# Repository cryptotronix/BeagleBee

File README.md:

BeagleBee
=========

Design files for the Cryptotronix BeagleBee Adapter available on [Tindie](https://www.tindie.com/products/cryptotronix/beaglebee/).

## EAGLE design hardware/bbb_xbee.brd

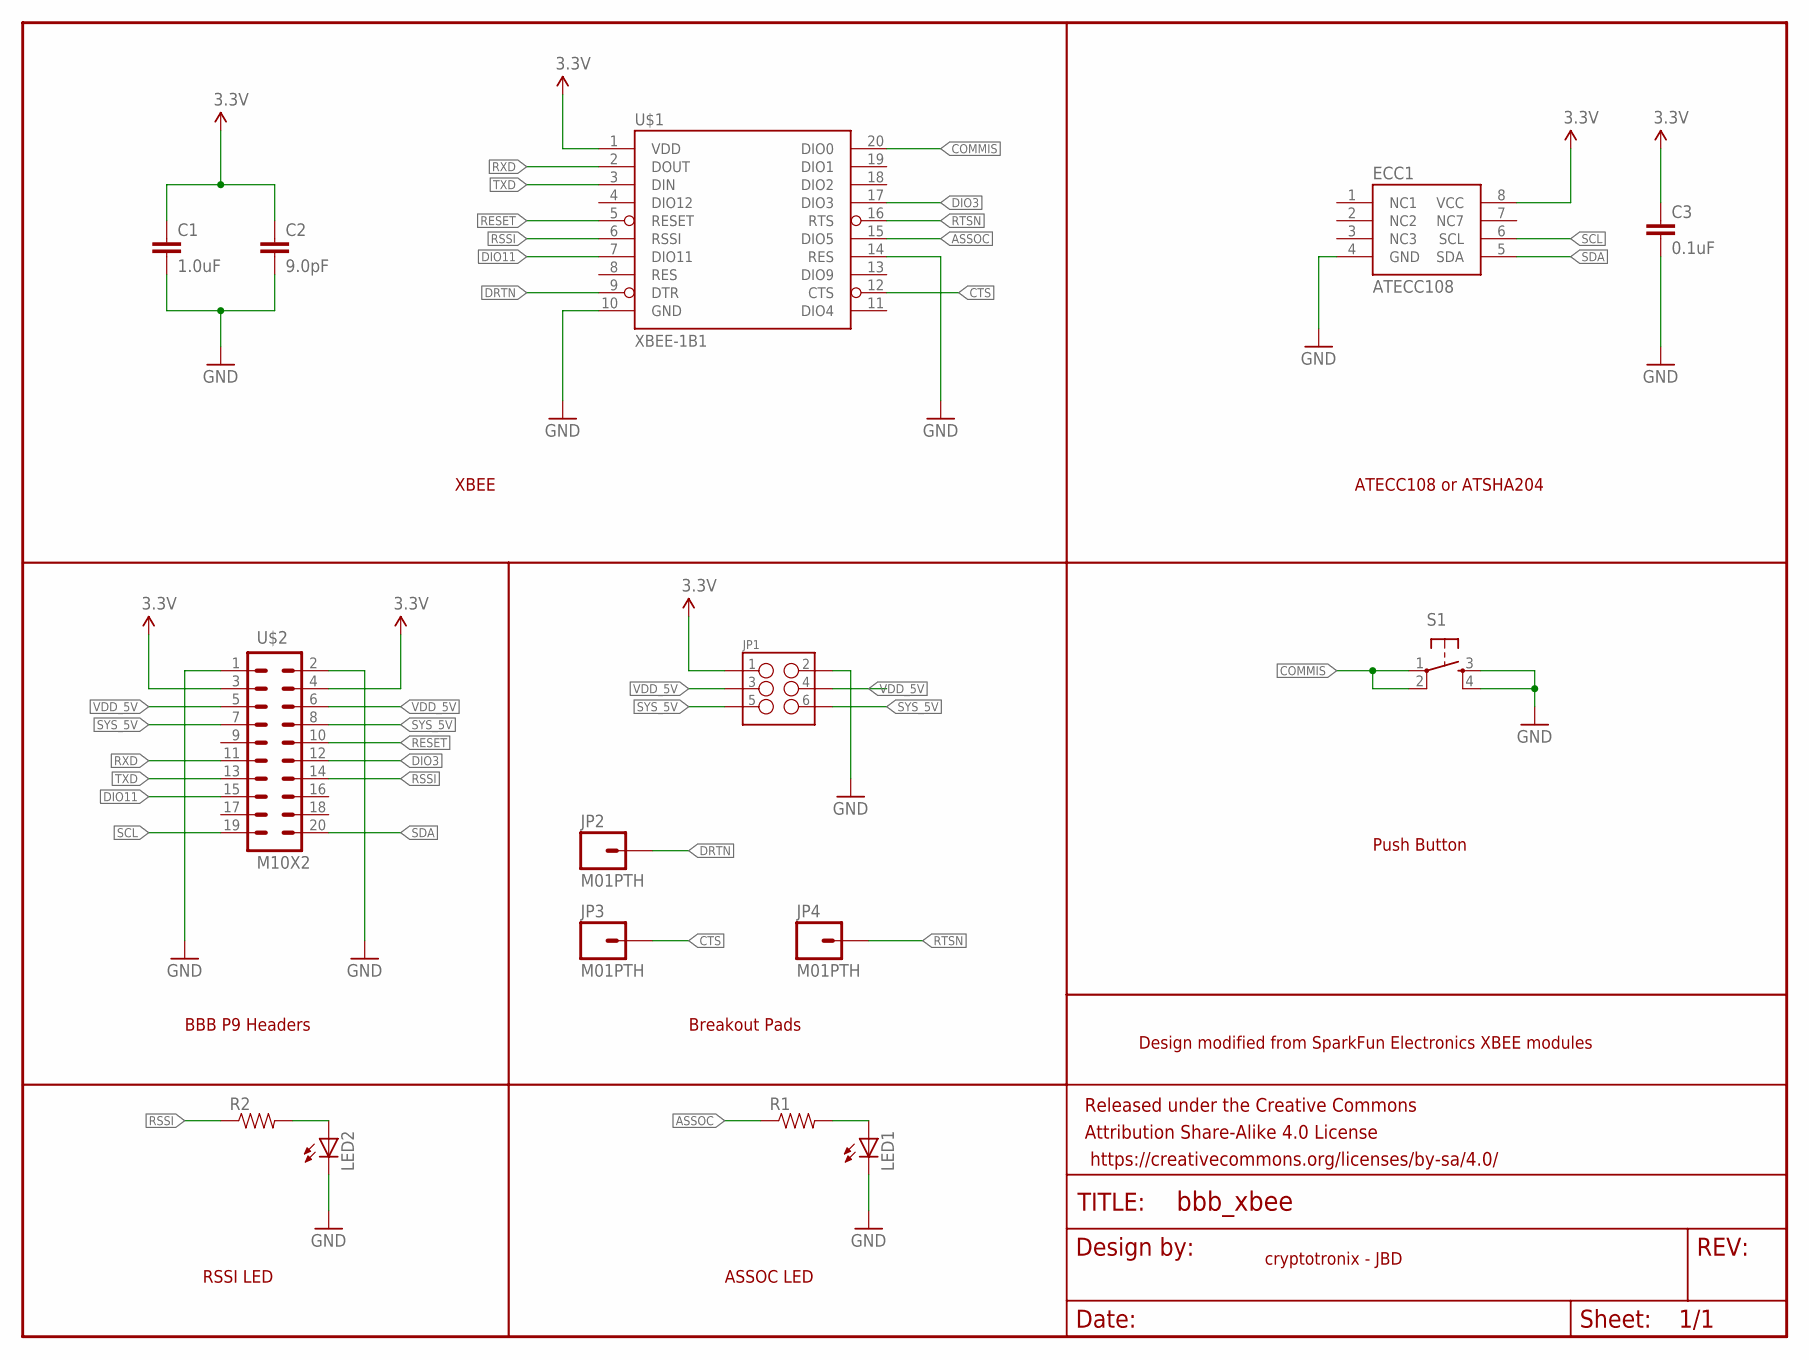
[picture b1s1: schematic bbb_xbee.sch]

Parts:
C1: 1.0uF; 0603-CAP
C2: 9.0pF; 0603-CAP
C3: 0.1uF; 0603-CAP
ECC1: ATECC108; SOIC8
FRAME1: FRAME-LETTER; CREATIVE_COMMONS
JP1: M03X22X3_SILK_SM; 2X3
JP2, JP3, JP4: M01PTH; 1X01
LED1: LED-RED0603; LED-0603
LED2: LED-BLUE0603; LED-0603
R1, R2: RESISTOR0603; 0603-RES
S1: TAC_SWITCHPTH; TACTILE-PTH
U$1: XBEE-1B1; XBEE-1
U$2: M10X2; 2X10

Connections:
3.3V: C1.1, C2.1, C3.1, ECC1.8 (VCC), JP1.1, U$1.1 (VDD), U$2.3, U$2.4
ASSOC: R1.1, U$1.15 (DIO5)
COMMIS: S1.1, S1.2, U$1.20 (DIO0)
CTS: JP3.1, U$1.12 (CTS)
DIO3: U$1.17 (DIO3), U$2.12
DIO11: U$1.7 (DIO11), U$2.15
DRTN: JP2.1, U$1.9 (DTR)
GND: C1.2, C2.2, C3.2, ECC1.4 (GND), JP1.2, LED1.C, LED2.C, S1.3, S1.4, U$1.10 (GND), U$1.14 (RES), U$2.1, U$2.2
unnamed: LED1.A, R1.2
unnamed: LED2.A, R2.2
RESET: U$1.5 (RESET), U$2.10
RSSI: R2.1, U$1.6 (RSSI), U$2.14
RTSN: JP4.1, U$1.16 (RTS)
RXD: U$1.2 (DOUT), U$2.11
SCL: ECC1.6 (SCL), U$2.19
SDA: ECC1.5 (SDA), U$2.20
SYS_5V: JP1.5, JP1.6, U$2.7, U$2.8
TXD: U$1.3 (DIN), U$2.13
VDD_5V: JP1.3, JP1.4, U$2.5, U$2.6

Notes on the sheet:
BBB P9 Headers
Breakout Pads
RSSI LED
ASSOC LED
Push Button
XBEE
ATECC108 or ATSHA204
cryptotronix - JBD
Design modified from SparkFun Electronics XBEE modules

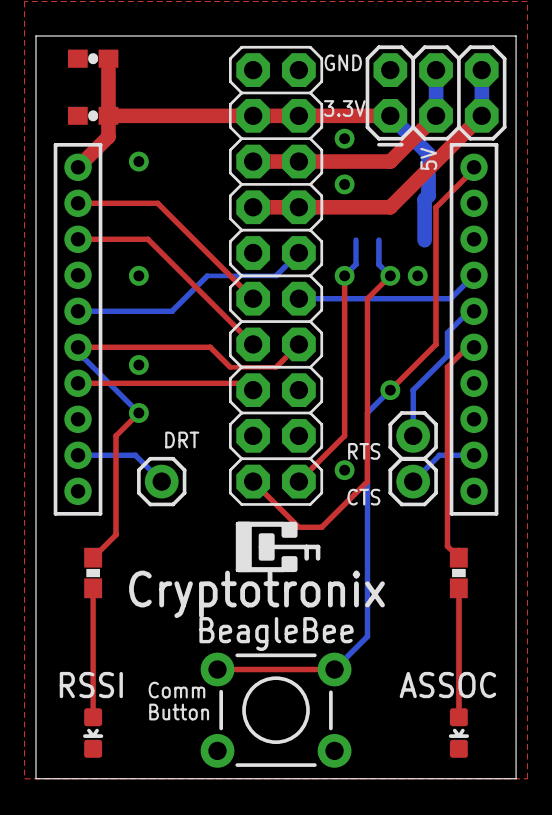
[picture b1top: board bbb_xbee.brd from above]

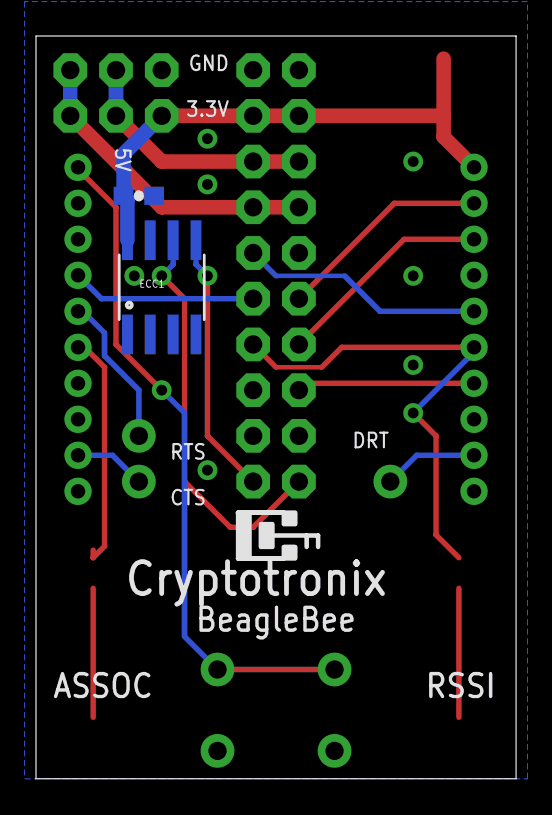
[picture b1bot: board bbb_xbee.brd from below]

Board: 2 copper layers, 26.7 x 41.3 mm, 16 parts (2 on the bottom side), 19 nets.

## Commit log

2014-05-09 Adds files.
2014-05-09 Adds schematic.

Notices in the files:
parts and their libraries:
SparkFun-RF: Licensing: Creative Commons ShareAlike 4.0 International - https://creativecommons.org/licenses/by-sa/4.0
SparkFun-Aesthetics: Released under the Creative Commons Attribution Share-Alike 4.0 License
SparkFun-Aesthetics: https://creativecommons.org/licenses/by-sa/4.0
